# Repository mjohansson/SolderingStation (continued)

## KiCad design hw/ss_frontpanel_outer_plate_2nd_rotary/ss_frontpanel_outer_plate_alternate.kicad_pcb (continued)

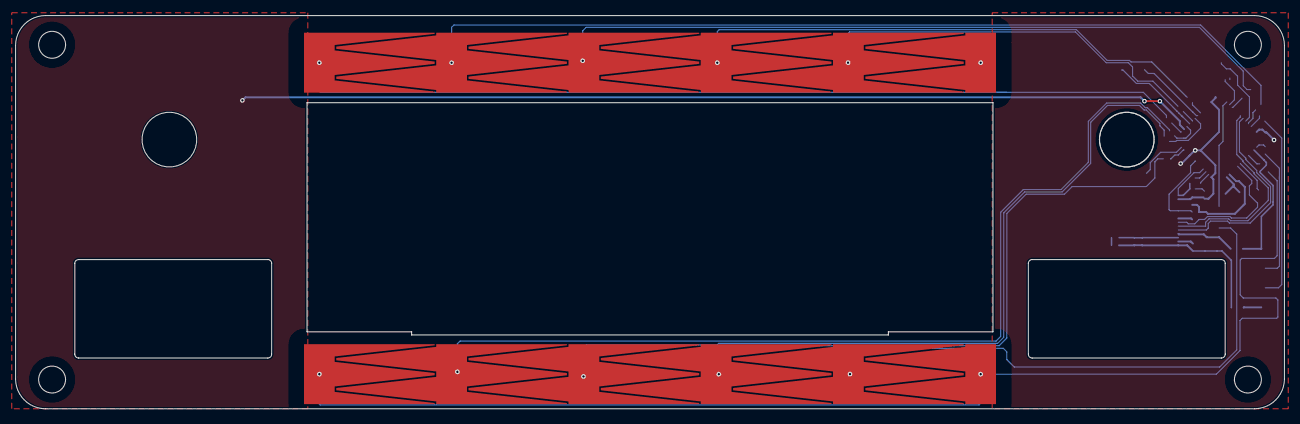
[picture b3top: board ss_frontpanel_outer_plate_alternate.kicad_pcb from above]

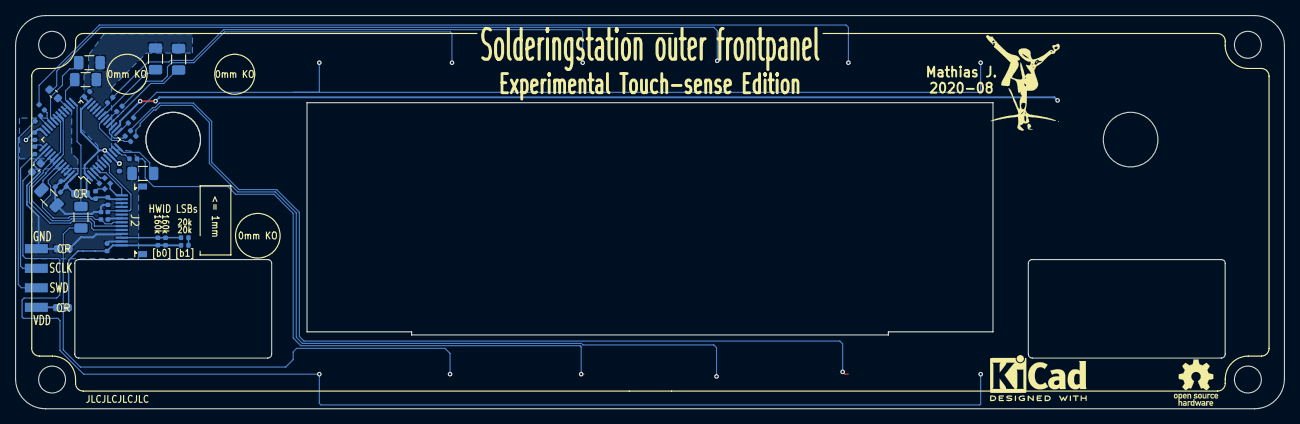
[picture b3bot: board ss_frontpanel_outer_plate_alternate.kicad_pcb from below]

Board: 2 copper layers, 165.0 x 51.1 mm, 51 parts (44 on the bottom side), 42 nets.

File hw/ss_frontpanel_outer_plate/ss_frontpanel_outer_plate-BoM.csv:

"Id";"Designator";"Package";"Quantity";"Designation";"Supplier and ref";
1;"H2,H3,H4,H1";"MountingHole_3.5mm_Hammond_panel_screws";4;"MountingHole";;;
2;"M1";"NHD3_12-Reverse_Bezel";1;"NHD3.12-Mechanical_window";;;
3;"LTS1,LTS2";"Touchsensor_linear_slider-5ch_H_90x8mm";2;"Touchsensor_linear_5ch_H";;;
4;"M2";"Frontpanel_L_Powerbtn_Pushbtns_outer_cutouts";1;"Mech_cutout_SS_left_pwrbtn_and_speedbtns";;;
5;"C1,C3,C12,C13,C15,C14";"C_0402_1005Metric";6;"100n";;;
6;"C6,C7,C8,C9,C4,C10";"C_1206_3216Metric";6;"47nF_COG";;;
7;"C17,C2";"C_0402_1005Metric";2;"10u";;;
8;"R1";"R_0402_1005Metric";1;"10k";;;
9;"R2,R6,R9,R5,R3,R4,R7,R10,R13,R20";"R_0402_1005Metric";10;"1k";;;
10;"R8,R11";"R_0603_1608Metric";2;"1k";;;
11;"R12";"R_1206_3216Metric";1;"1k";;;
12;"M3";"Frontpanel_R_RotaryEnc_Pushbtns_outer_cutouts";1;"Mech_cutout_SS_right_rotary_and_speedbtns";;;
13;"J2";"FPC_14p_05mm-WE_687114182122";1;"FFC_conn_14p";;;
14;"R17,R16";"R_0402_1005Metric";2;"160k";;;
15;"R18,R19,R14";"R_0603_1608Metric";3;"0R";;;
16;"J1";"4pin_SWD_SMT_100mil";1;"Conn_01x04";;;
17;"Logo1";"MJ_10.3x12.7";1;"Logo_MJ";;;
18;"Logo2";"OSHW-Logo_5.7x6mm_SilkScreen";1;"Logo_Open_Hardware_Small";;;
19;"Logo3";"KiCad-Logo2_5mm_SilkScreen";1;"Logo_Kicad";;;
20;"U1";"LQFP-48_7x7mm_P0.5mm";1;"STM32L052C8Tx";;;
21;"D1";"SX_0402_RGB-CA-06";1;"SX_0402_RGB-LED_CA";;;
22;"R15,R21";"R_0402_1005Metric";2;"20k";;;
